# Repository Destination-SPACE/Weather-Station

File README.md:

# Destination Weather Station
The Destination Weather Station is a low cost Arduino based platfrom that collects, and displays weather data. Check out the [wiki](https://github.com/Destination-SPACE/Weather-Station/wiki) for step-by-step instructions.

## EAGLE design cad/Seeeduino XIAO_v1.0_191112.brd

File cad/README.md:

# Weather Station CAD
Here are the schematic and PCB files for the Seeeduino XIAO

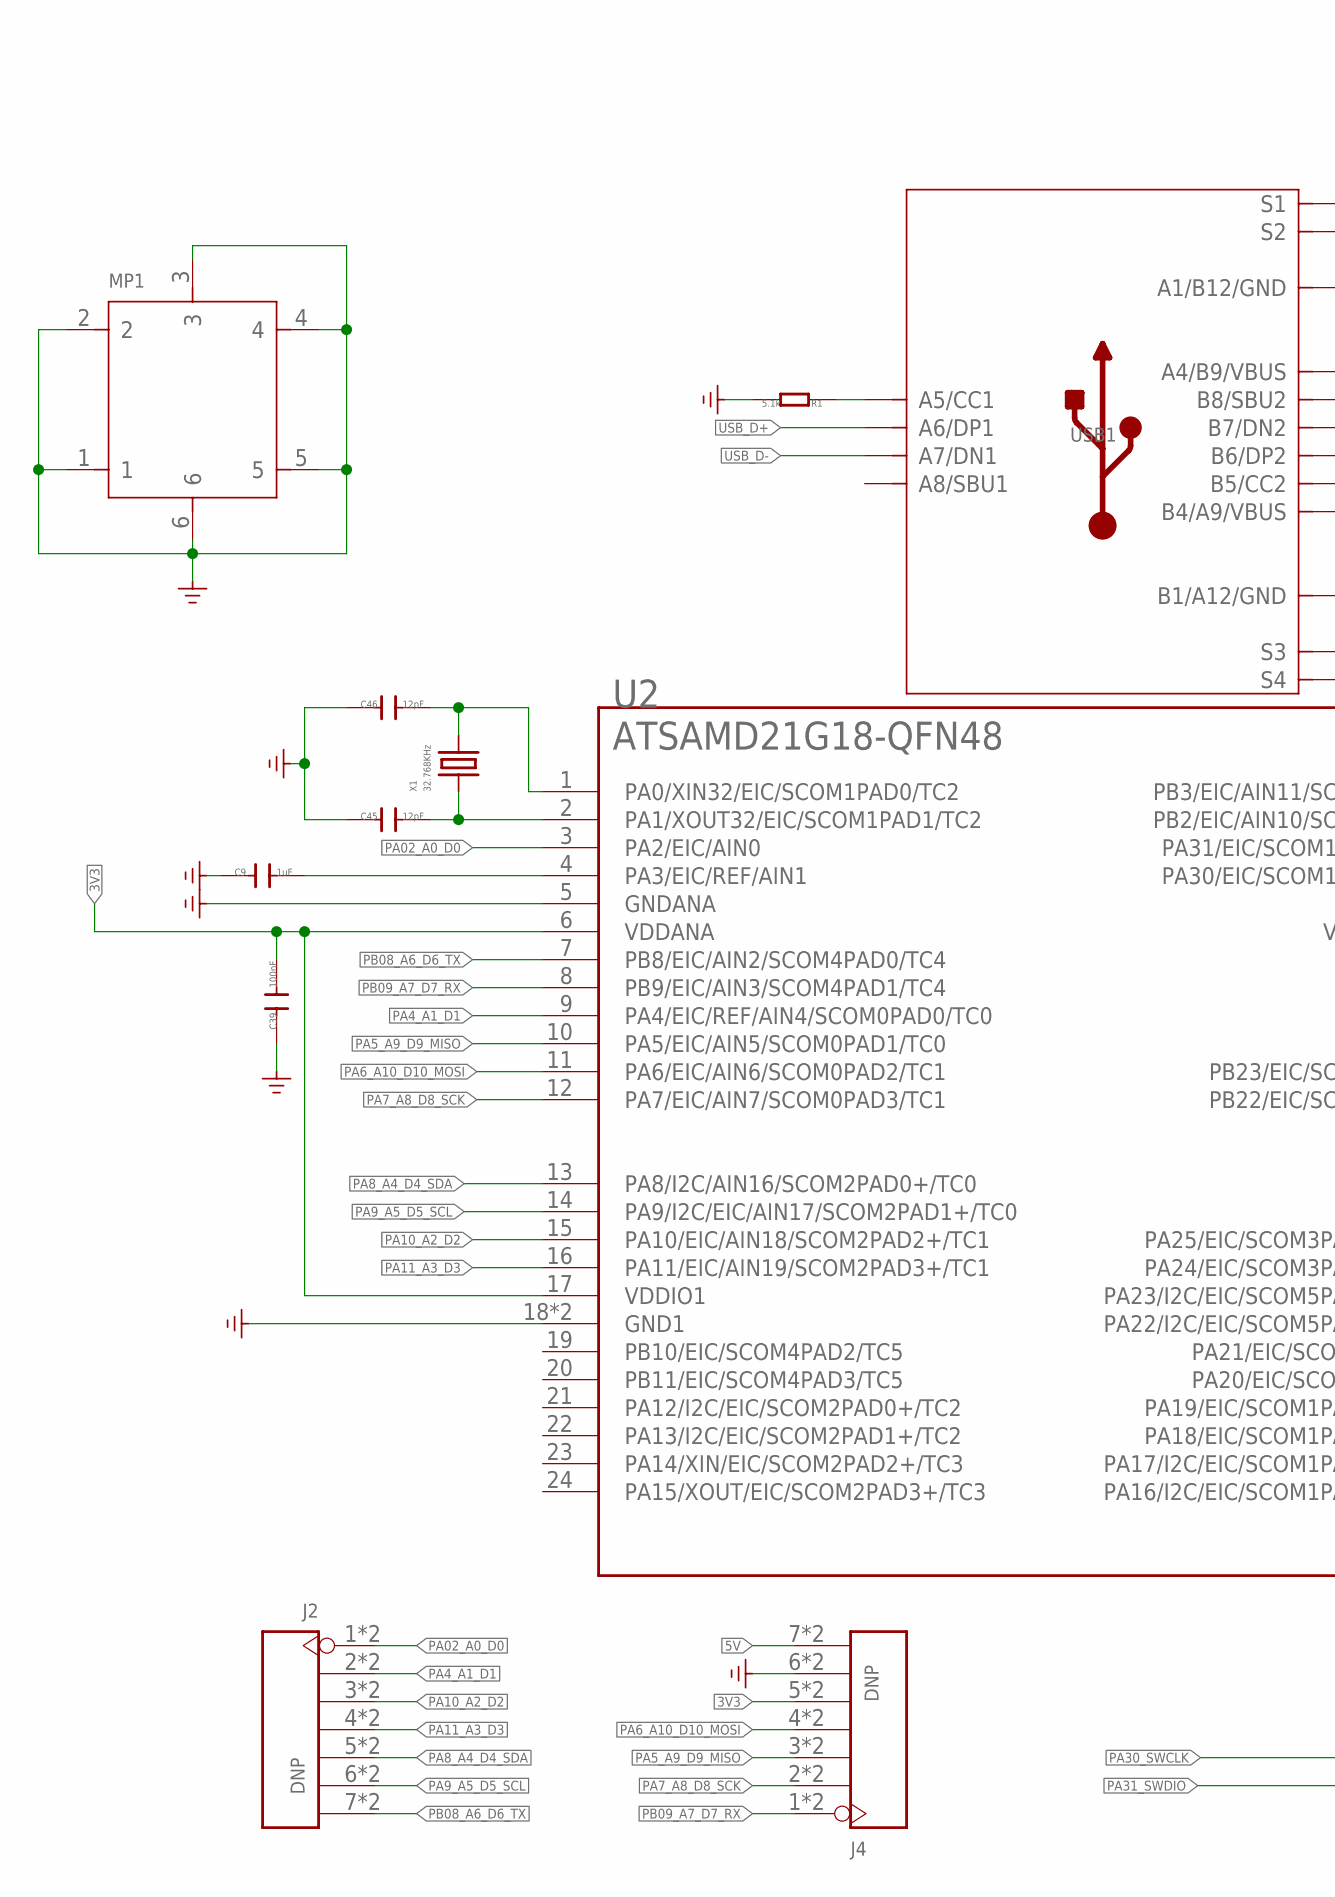
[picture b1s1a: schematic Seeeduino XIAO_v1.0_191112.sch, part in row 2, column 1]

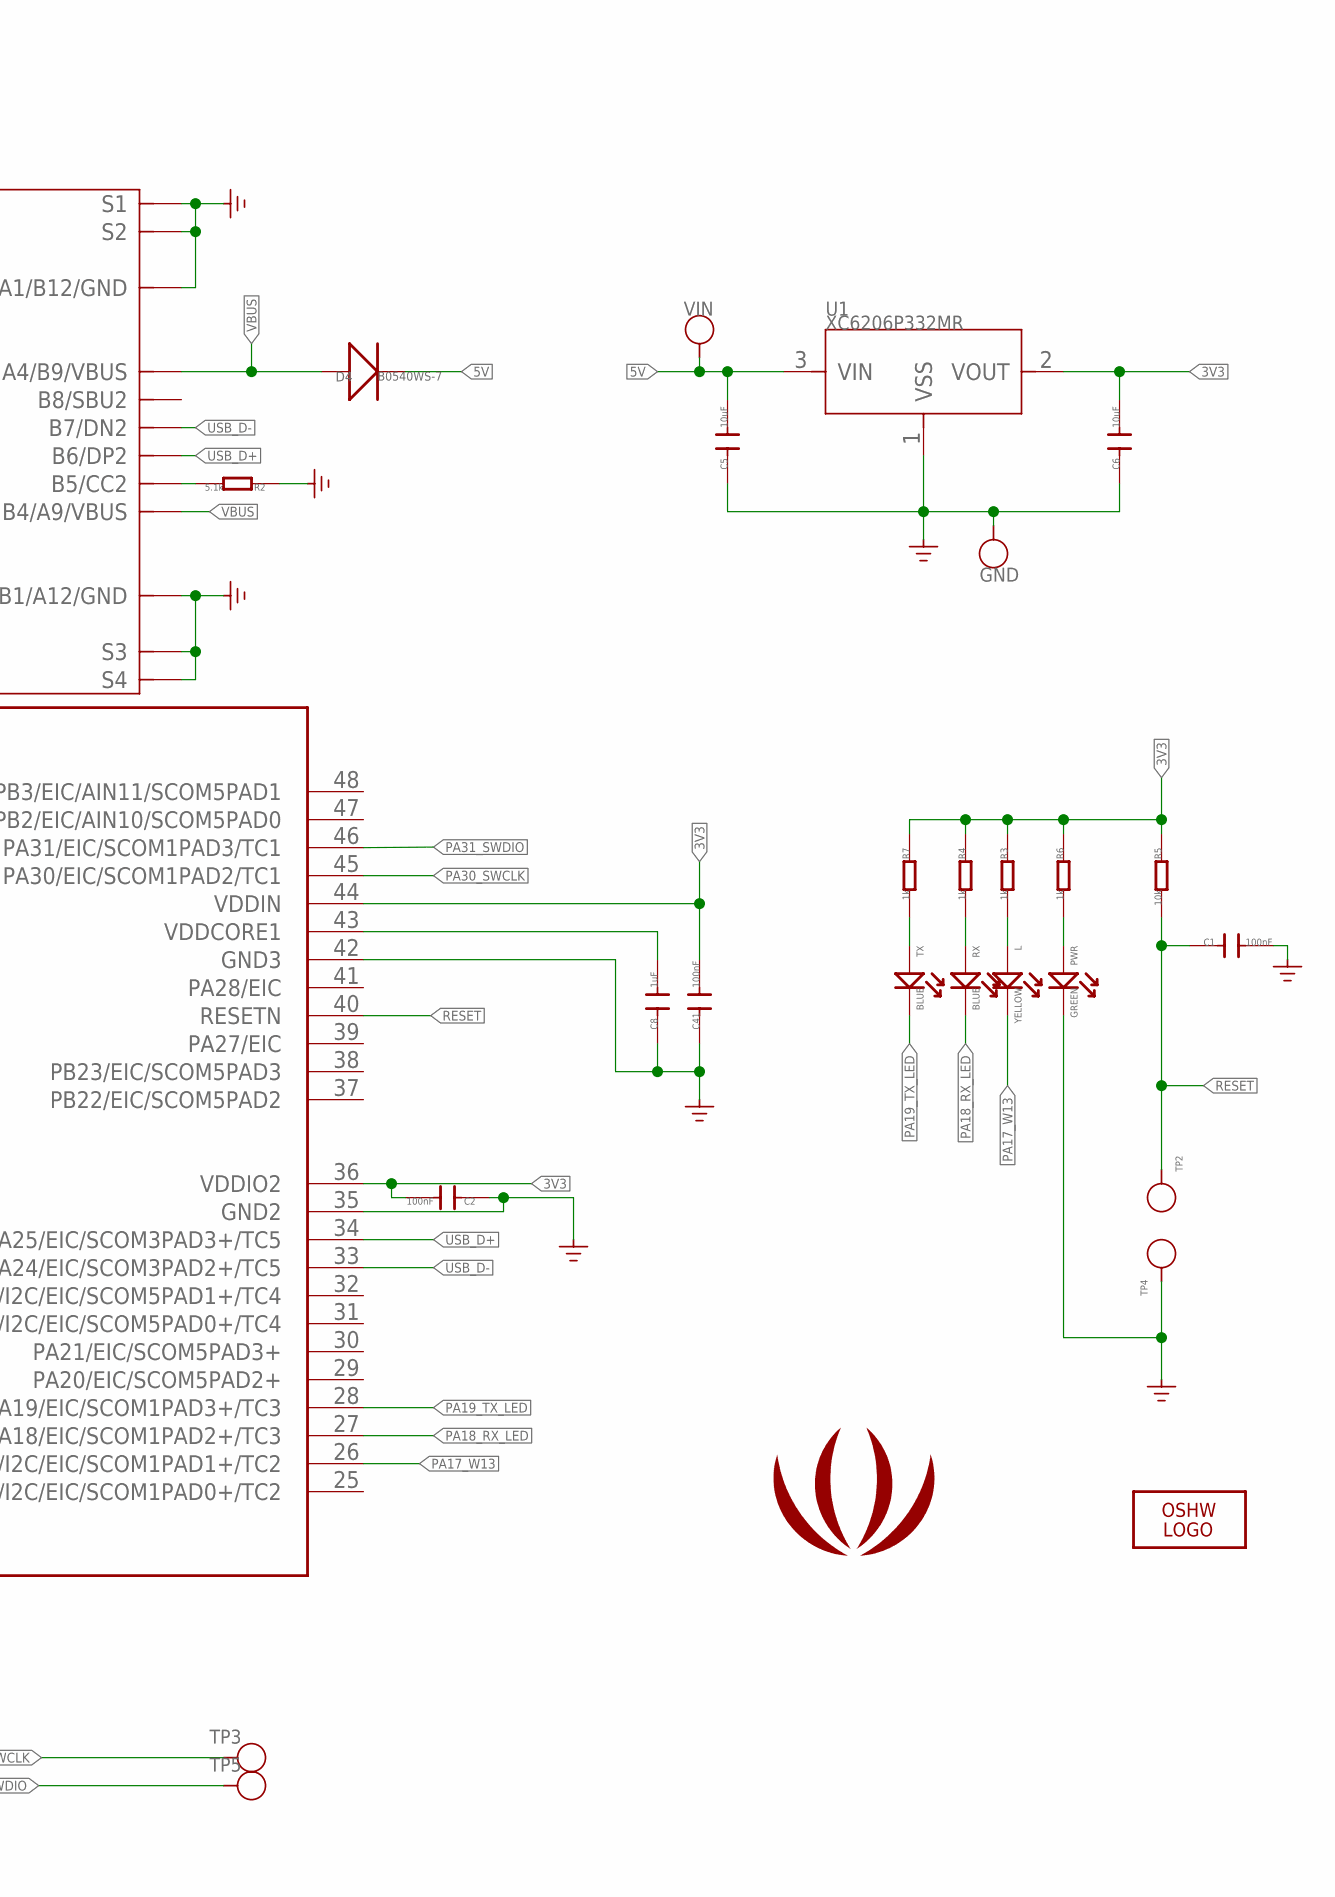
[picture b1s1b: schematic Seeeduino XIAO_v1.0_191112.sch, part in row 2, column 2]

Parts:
C1, C2, C39, C41: 100nF; C0402
C5, C6: 10uF; C0603
C8, C9: 1uF; C0402
C45, C46: 12pF; C0402
D4: B0540WS-7; SOD323
GND: TEST-POINT'4080'; TP-80X40MIL
J2, J4: DNP; H7-HALF-HOLE-2.54
L: YELLOW; LED-0402
LOGO1: LOGO-OSHW-FILLX0200-NT; OSHW_FILLX200_NOTEXT
MP1: SHIELDING-COVER-12.3X11.9X0.2MM
PWR: GREEN; LED-0402
R1, R2: 5.1k; R0402
R3, R4, R6, R7: 1k; R0402
R5: 10k; R0402
RX: BLUE; LED-0402
TP2, TP3, TP4, TP5: TEST-POINT'4545'; TP-D45MIL
TX: BLUE; LED-0402
U1: XC6206P332MR; SOT-23
U2: ATSAMD21G18-QFN48; QFN48-7X7
U$3: LOGO-SEEED-BIG-SILK; SEEED-SILK-280*268MIL
USB1: USB2.0-TYPE-C
VIN: TEST-POINT'4080'; TP-80X40MIL
X1: 32.768KHz; X2-SMD-L2.0X1.2X0.55MM

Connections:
3V3: C2.2, C6.2, C39.2, C41.2, J4.5, J4.17 (5), R3.1, R4.1, R5.1, R6.1, R7.1, U1.2 (VOUT), U2.6 (VDDANA), U2.17 (VDDIO1), U2.36 (VDDIO2), U2.44 (VDDIN)
5V: C5.2, D4.-, J4.7, J4.19 (7), U1.3 (VIN), VIN.1
GND: C1.2, C2.1, C5.1, C6.1, C8.1, C9.1, C39.1, C41.1, C45.1, C46.1, GND.1, J4.6, J4.18 (6), MP1.1, MP1.2, MP1.3, MP1.4, MP1.5, MP1.6, PWR.-, R1.2, R2.1, TP4.T, U1.1 (VSS), U2.5 (GNDANA), U2.18 (GND1), U2.35 (GND2), U2.42 (GND3), U2.PAD (GND1), USB1.A1_B12 (A1/B12/GND), USB1.B1_A12 (B1/A12/GND), USB1.S1, USB1.S2, USB1.S3, USB1.S4, USB1.S5 (S1), USB1.S6 (S2)
unnamed: R1.1, USB1.A5 (A5/CC1)
unnamed: R2.2, USB1.B5 (B5/CC2)
unnamed: C8.2, U2.43 (VDDCORE1)
unnamed: C9.2, U2.4 (PA3/EIC/REF/AIN1)
unnamed: L.+, R3.2
unnamed: R7.2, TX.+
unnamed: C45.2, U2.2 (PA1/XOUT32/EIC/SCOM1PAD1/TC2), X1.2
unnamed: R4.2, RX.+
unnamed: C46.2, U2.1 (PA0/XIN32/EIC/SCOM1PAD0/TC2), X1.1
unnamed: PWR.+, R6.2
PA02_A0_D0: J2.1, J2.13 (1), U2.3 (PA2/EIC/AIN0)
PA4_A1_D1: J2.2, J2.14 (2), U2.9 (PA4/EIC/REF/AIN4/SCOM0PAD0/TC0)
PA5_A9_D9_MISO: J4.3, J4.15 (3), U2.10 (PA5/EIC/AIN5/SCOM0PAD1/TC0)
PA6_A10_D10_MOSI: J4.4, J4.16 (4), U2.11 (PA6/EIC/AIN6/SCOM0PAD2/TC1)
PA7_A8_D8_SCK: J4.2, J4.14 (2), U2.12 (PA7/EIC/AIN7/SCOM0PAD3/TC1)
PA8_A4_D4_SDA: J2.5, J2.17 (5), U2.13 (PA8/I2C/AIN16/SCOM2PAD0+/TC0)
PA9_A5_D5_SCL: J2.6, J2.18 (6), U2.14 (PA9/I2C/EIC/AIN17/SCOM2PAD1+/TC0)
PA10_A2_D2: J2.3, J2.15 (3), U2.15 (PA10/EIC/AIN18/SCOM2PAD2+/TC1)
PA11_A3_D3: J2.4, J2.16 (4), U2.16 (PA11/EIC/AIN19/SCOM2PAD3+/TC1)
PA17_W13: L.-, U2.26 (PA17/I2C/EIC/SCOM1PAD1+/TC2)
PA18_RX_LED: RX.-, U2.27 (PA18/EIC/SCOM1PAD2+/TC3)
PA19_TX_LED: TX.-, U2.28 (PA19/EIC/SCOM1PAD3+/TC3)
PA30_SWCLK: TP3.T, U2.45 (PA30/EIC/SCOM1PAD2/TC1)
PA31_SWDIO: TP5.T, U2.46 (PA31/EIC/SCOM1PAD3/TC1)
PB08_A6_D6_TX: J2.7, J2.19 (7), U2.7 (PB8/EIC/AIN2/SCOM4PAD0/TC4)
PB09_A7_D7_RX: J4.1, J4.13 (1), U2.8 (PB9/EIC/AIN3/SCOM4PAD1/TC4)
RESET: C1.1, R5.2, TP2.T, U2.40 (RESETN)
USB_D+: U2.34 (PA25/EIC/SCOM3PAD3+/TC5), USB1.A6 (A6/DP1), USB1.B6 (B6/DP2)
USB_D-: U2.33 (PA24/EIC/SCOM3PAD2+/TC5), USB1.A7 (A7/DN1), USB1.B7 (B7/DN2)
VBUS: D4.+, USB1.A4_B9 (A4/B9/VBUS), USB1.B4_A9 (B4/A9/VBUS)

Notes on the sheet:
2019.11.12
Jienian.Feng
v1.0
Initail Version

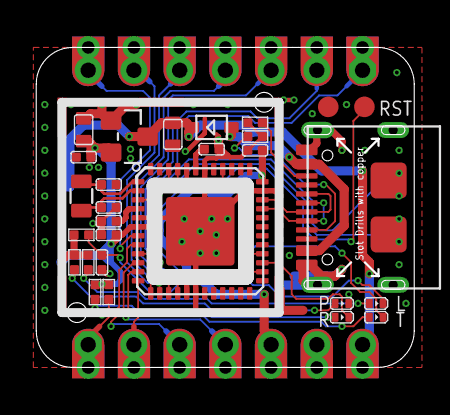
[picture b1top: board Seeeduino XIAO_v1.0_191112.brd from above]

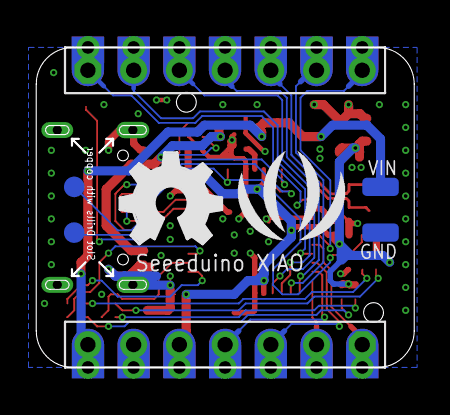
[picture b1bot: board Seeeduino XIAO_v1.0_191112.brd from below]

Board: 2 copper layers, 21.0 x 17.8 mm, 37 parts (6 on the bottom side), 33 nets.

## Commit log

2021-05-23 Rename README to README.md
2021-08-23 Create LICENSE
2021-09-03 outdated
2021-09-03 Fixed Schematic
2021-09-03 Added SAMD21G18 Datasheet
2021-09-03 Created CAD subfolder
2021-09-03 created subfolder for sample data
2021-09-03 sample dataset for weather station
2021-09-03 updated schematic in instructions
2021-09-03 added CERN OHL
2021-09-06 replaced license
